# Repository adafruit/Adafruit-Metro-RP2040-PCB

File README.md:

## Adafruit Metro RP2040 PCB

<a href="http://www.adafruit.com/products/5786"><br/>
Click here to purchase one from the Adafruit shop</a>

PCB files for the Adafruit Metro RP2040. 

Format is EagleCAD schematic and board layout
* https://www.adafruit.com/product/5786

### Description

Choo! Choo! This is the RP2040 Metro Line, making all station stops at "Dual Cortex M0+ mountain", "264K RAM round-about" and "16 Megabytes of Flash town". This train is pile high with hardware that complements the Raspberry Pi RP2040 chip to make it an excellent development board for projects that want Arduino-shape-compatibility or just need the extra space and debugging ports.

* RP2040 main chip, 133MHz clock, 3.3V logic
* 16 MB of QSPI flash for program storage
* 24 GPIO, 4 of which are also analog inputs
* Micro SD card wired up for SPI interfacing, also has extra pins connected for advanced-user SDIO interfacing (note that there's no released usage code for SDIO in Arduino/Python, so this is a super-cutting-edge setup)
* Onboard RGB NeoPixel
* Onboard #13 LED
* Stemma QT port for I2C peripherals and sensors
* Reset and Boot buttons on PCB edge
* Pico Probe debug port - 3 pin JST SH compatible
* SWD debug port - 2x5 0.05" standard connector
* USB Type C power and data
* 5.5mm / 2.1mm DC jack for 6-12VDC power
* On/off switch for DC jack
* GPIO pin numbers match classic Arduino pins, other than A4/A5 which are D24 and D25 (there's only 4 ADC pins on the RP2040)
* RX / TX switch for swapping D0 and D1 locations

You may be wondering about the RX-TX switch: we added this because traditional Arduino board start counting the GPIO for the digital pins with 0-7 and then 8-13. However, the D0/D1 pins are also traditionally the hardware UART Serial1, where D0 is Rx and D1 is Tx. On the RP2040, however, the UART pins are the other around: D0 is Tx and D1 is Rx. Thus a DPDT switch: flip one way to have the GPIO go in order of 0-7, flip the other way to have the logical locations of the hardware UART correct but now the pin order is 1, 0, 2, 3..7. Of course, it's also handy if, like us, you often swap the pins - now you don't need to require or cut/solder traces!
About the RP2040

The RP2040 is a powerful chip, which has the clock speed of our M4 (SAMD51), and two cores that are equivalent to our M0 (SAMD21). Since it is an M0 chip, it does not have a floating point unit or DSP hardware support - so if you're doing something with heavy floating-point math, it will be done in software and thus not as fast as an M4. For many other computational tasks, you'll get close-to-M4 speeds!

For peripherals, there are two I2C controllers, two SPI controllers, and two UARTs that are multiplexed across the GPIO - check the pinout for what pins can be set to which. There are 16 PWM channels, each pin has a channel it can be set to (ditto on the pinout).

You'll note there's no I2S peripheral, or SDIO, or camera, what's up with that? Well, instead of having specific hardware support for serial-data-like peripherals like these, the RP2040 comes with the PIO state machine system, which is a unique and powerful way to create custom hardware logic and data processing blocks that run on their own without taking up a CPU. For example, NeoPixels - often we bitbang the timing-specific protocol for these LEDs. For the RP2040, we instead use PIO object that reads in the data buffer and clocks out the right bitstream with perfect accuracy. Same with I2S audio in or out, LED matrix displays, 8-bit or SPI based TFTs, even VGA! In MicroPython and CircuitPython, you can create PIO control commands to script the peripheral and load it in at runtime. There are 2 PIO peripherals with 4 state machines each.

There is great C/C++ support, unofficial (but really good) Arduino support, an official MicroPython port, and a CircuitPython port! We, of course, recommend CircuitPython because we think it's the easiest way to get started, and it has support with most of our drivers, displays, sensors, and more, supported out of the box so you can follow along with our CircuitPython projects and tutorials.

While the RP2040 has lots of onboard RAM (264KB), it does not have built-in FLASH memory. Instead, that is provided by the external QSPI flash chip. On this board, there is 16 MB, which is shared between the program it's running and any file storage used by MicroPython or CircuitPython. When using C/C++, you get the whole flash memory, if using Python, you will have about 7 MB remaining for code, files, images, fonts, etc.
RP2040 Chip features:

* Dual ARM Cortex-M0+ @ 133MHz
* 264kB on-chip SRAM in six independent banks
* Support for up to 16MB of off-chip Flash memory via dedicated QSPI bus
* DMA controller
* Fully-connected AHB crossbar
* Interpolator and integer divider peripherals
* On-chip programmable LDO to generate core voltage
* 2 on-chip PLLs to generate USB and core clocks
* 30 GPIO pins, 4 of which can be used as analog inputs
* Peripherals
  * 2 UARTs
  * 2 SPI controllers
  * 2 I2C controllers
  * 16 PWM channels
  * USB 1.1 controller and PHY, with host and device support
  * 8 PIO state machines

### License

Adafruit invests time and resources providing this open source design, please support Adafruit and open-source hardware by purchasing products from [Adafruit](https://www.adafruit.com)!

Designed by Limor Fried/Ladyada for Adafruit Industries.

Creative Commons Attribution/Share-Alike, all text above must be included in any redistribution. 
See license.txt for additional details.

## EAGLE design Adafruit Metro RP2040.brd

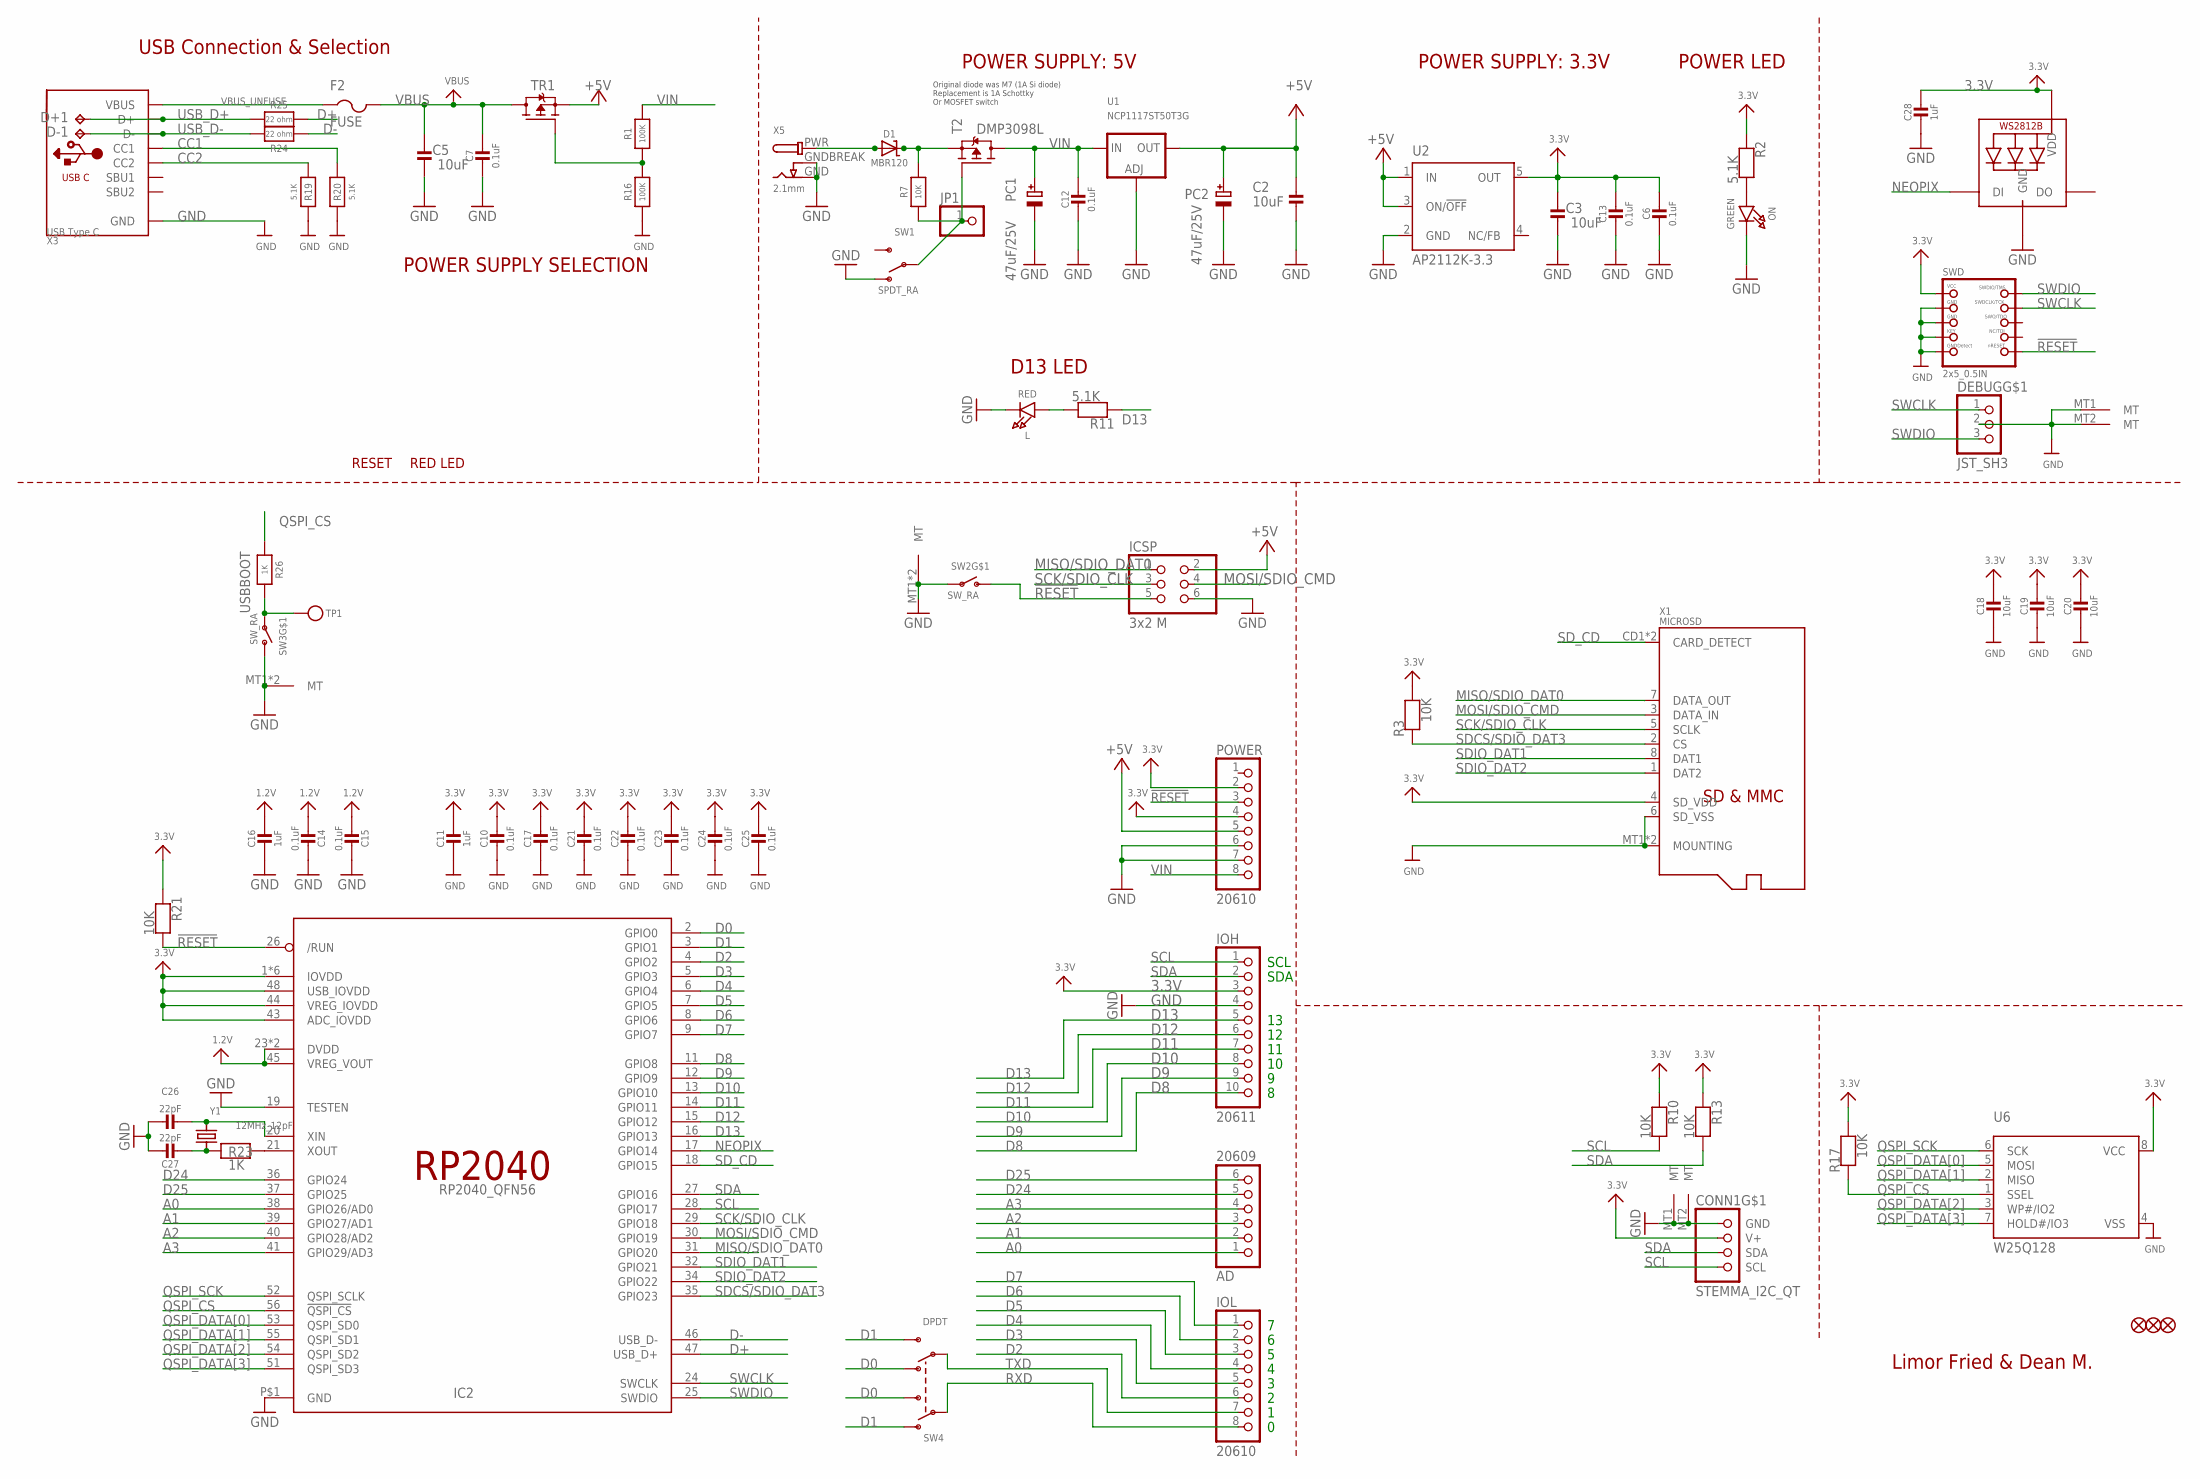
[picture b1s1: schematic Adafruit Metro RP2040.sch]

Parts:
AD: 20609; 1X06_OVALWAVE
C2, C3, C5, C18, C19, C20: 10uF; 0805-NO
C6, C7, C10, C12, C13, C14, C15, C17, C21, C22, C23, C24, C25: 0.1uF; 0603-NO
C11, C16, C28: 1uF; 0603-NO
C26, C27: 22pF; 0603-NO
CONN1: STEMMA_I2C_QT; JST_SH4
D1: MBR120; SOD-123
D+1: TPB1,27; B1,27
D-1: TPB1,27; B1,27
DEBUG: JST_SH3
F2: FUSE; R1206
FD1, FD2, FD3: FIDUCIAL_1MM
IC2: RP2040_QFN56; QFN56_7MM_REDUCEDEPAD
ICSP: 3x2 M; 2X03_ROUND_70MIL
IOH: 20611; 1X10_OVALWAVE
IOL: 20610; 1X08_OVALWAVE
JP1: HEADER-1X1ROUND; 1X01_ROUND
L: RED; CHIPLED_0603_NOOUTLINE
LED2: WS2812B_3535FULL; LED3535_FULLPADS
ON: GREEN; CHIPLED_0603_NOOUTLINE
PC1, PC2: 47uF/25V; PANASONIC_D
POWER: 20610; 1X08_OVALWAVE
R1, R16: 100K; 0603-NO
R2, R11, R19, R20: 5.1K; 0603-NO
R3, R7, R10, R13, R17, R21: 10K; 0603-NO
R23, R26: 1K; 0603-NO
R24, R25: 22 ohm; 0603-NO
SW1: SPDT_RA; SPDT_SMT_SSSS811101
SW2, SW3: SW_RA; SPST_TACTILE_RA
SW4: DPDT; EG1390
SWD: 2x5_0.5IN; 2X05_1.27MM_BOX_POSTS
T2: DMP3098L; SOT23-WIDE
TP1: TESTPOINTROUND1.5MMNO; TESTPOINT_ROUND_1.5MM_NO
TR1: DMP3098L; SOT23-WIDE
U1: NCP1117ST50T3G; SOT223-R
U2: AP2112K-3.3; SOT23-DBV
U6: W25Q128; SOIC8_208MIL
X1: MICROSD
X3: USB Type C; USB_C_CUSB31-CFM2AX-01-X
X5: 2.1mm; DCJACK_2MM_PTH
Y1: 12MHz_12pF; CRYSTAL_2.5X2

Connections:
1.2V: C14.2, C15.2, C16.1, IC2.23 (DVDD), IC2.45 (VREG_VOUT), IC2.50 (DVDD)
3.3V: C3.2, C6.2, C10.1, C11.1, C13.1, C17.1, C18.1, C19.1, C20.1, C21.1, C22.1, C23.1, C24.1, C25.1, C28.1, CONN1.2 (V+), IC2.1 (IOVDD), IC2.10 (IOVDD), IC2.22 (IOVDD), IC2.33 (IOVDD), IC2.42 (IOVDD), IC2.43 (ADC_IOVDD), IC2.44 (VREG_IOVDD), IC2.48 (USB_IOVDD), IC2.49 (IOVDD), IOH.3, LED2.2 (VDD), POWER.2, POWER.4, R2.1, R3.2, R10.1, R13.1, R17.2, R21.1, SWD.1 (VCC), U2.5 (OUT), U6.8 (VCC), X1.4 (SD_VDD)
!RESET: IC2.26 (/RUN), ICSP.5, POWER.3, R21.2, SW2.2 (S), SWD.10 (NRESET)
+5V: C2.2, ICSP.2, PC2.+, POWER.5, TR1.2 (S), U1.2 (OUT), U1.4 (OUT), U2.1 (IN), U2.3 (ON/!OFF)
A0: AD.1, IC2.38 (GPIO26/AD0)
A1: AD.2, IC2.39 (GPIO27/AD1)
A2: AD.3, IC2.40 (GPIO28/AD2)
A3: AD.4, IC2.41 (GPIO29/AD3)
CC1: R20.2, X3.A5 (CC1)
CC2: R19.2, X3.B5 (CC2)
D0: IC2.2 (GPIO0), SW4.O2, SW4.S1
D1: IC2.3 (GPIO1), SW4.O1, SW4.S2
D2: IC2.4 (GPIO2), IOL.6
D3: IC2.5 (GPIO3), IOL.5
D4: IC2.6 (GPIO4), IOL.4
D5: IC2.7 (GPIO5), IOL.3
D6: IC2.8 (GPIO6), IOL.2
D7: IC2.9 (GPIO7), IOL.1
D8: IC2.11 (GPIO8), IOH.10
D9: IC2.12 (GPIO9), IOH.9
D10: IC2.13 (GPIO10), IOH.8
D11: IC2.14 (GPIO11), IOH.7
D12: IC2.15 (GPIO12), IOH.6
D13: IC2.16 (GPIO13), IOH.5, R11.1
D24: AD.5, IC2.36 (GPIO24)
D25: AD.6, IC2.37 (GPIO25)
D+: IC2.47 (USB_D+), R25.2
D-: IC2.46 (USB_D-), R24.2
GND: C2.1, C3.1, C5.1, C6.1, C7.2, C10.2, C11.2, C12.2, C13.2, C14.1, C15.1, C16.2, C17.2, C18.2, C19.2, C20.2, C21.2, C22.2, C23.2, C24.2, C25.2, C26.1, C27.1, C28.2, CONN1.1 (GND), CONN1.MT1 (MT), CONN1.MT2 (MT), DEBUG.2, DEBUG.MT1 (MT), DEBUG.MT2 (MT), IC2.19 (TESTEN), IC2.P$1 (GND), ICSP.6, IOH.4, L.C, LED2.4 (GND), ON.C, PC1.-, PC2.-, POWER.6, POWER.7, R16.1, R19.1, R20.1, SW1.A (O), SW2.1, SW2.MT1 (MT), SW2.MT2 (MT), SW3.2 (S), SW3.MT1 (MT), SW3.MT2 (MT), SWD.3 (GND), SWD.5 (GND), SWD.7 (KEY), SWD.9 (GNDDETECT), U1.1 (ADJ), U2.2 (GND), U6.4 (VSS), X1.6 (SD_VSS), X1.MT1 (MOUNTING), X1.MT2 (MOUNTING), X3.A1B12 (GND), X3.B1A12 (GND), X5.GND, X5.GNDBREAK
MISO/SDIO_DAT0: IC2.31 (GPIO20), ICSP.1, X1.7 (DATA_OUT)
MOSI/SDIO_CMD: IC2.30 (GPIO19), ICSP.4, X1.3 (DATA_IN)
unnamed: L.A, R11.2
unnamed: ON.A, R2.2
unnamed: C26.2, IC2.20 (XIN), Y1.3 (2)
unnamed: C27.2, R23.1, Y1.1
unnamed: R1.1, R16.2, TR1.1 (G)
unnamed: IC2.21 (XOUT), R23.2
unnamed: D1.C, R7.2, T2.2 (S)
NEOPIX: IC2.17 (GPIO14), LED2.1 (DI)
PWRIN: D1.A, X5.PWR
PWR_SWITCH: JP1.1, R7.1, SW1.B, T2.1 (G)
QSPI_CS: IC2.56 (!QSPI_CS), R17.1, R26.1, U6.1 (SSEL)
QSPI_DATA[0]: IC2.53 (QSPI_SD0), U6.5 (MOSI)
QSPI_DATA[1]: IC2.55 (QSPI_SD1), U6.2 (MISO)
QSPI_DATA[2]: IC2.54 (QSPI_SD2), U6.3 (WP#/IO2)
QSPI_DATA[3]: IC2.51 (QSPI_SD3), U6.7 (HOLD#/IO3)
QSPI_SCK: IC2.52 (QSPI_SCLK), U6.6 (SCK)
RXD: IOL.8, SW4.P1
SCK/SDIO_CLK: IC2.29 (GPIO18), ICSP.3, X1.5 (SCLK)
SCL: CONN1.4 (SCL), IC2.28 (GPIO17), IOH.1, R10.2
SDA: CONN1.3 (SDA), IC2.27 (GPIO16), IOH.2, R13.2
SDCS/SDIO_DAT3: IC2.35 (GPIO23), R3.1, X1.2 (CS)
SDIO_DAT1: IC2.32 (GPIO21), X1.8 (DAT1)
SDIO_DAT2: IC2.34 (GPIO22), X1.1 (DAT2)
SD_CD: IC2.18 (GPIO15), X1.CD1 (CARD_DETECT), X1.CD2 (CARD_DETECT)
SWCLK: DEBUG.1, IC2.24 (SWCLK), SWD.4 (SWDCLK)
SWDIO: DEBUG.3, IC2.25 (SWDIO), SWD.2 (SWDIO)
TXD: IOL.7, SW4.P2
USBBOOT: R26.2, SW3.1, TP1.P$1
USB_D+: D+1.TP, R25.1, X3.A6 (D+), X3.B6 (D+)
USB_D-: D-1.TP, R24.1, X3.A7 (D-), X3.B7 (D-)
VBUS: C5.2, C7.1, F2.2, TR1.3 (D)
VBUS_UNFUSE: F2.1, X3.A4B9 (VBUS), X3.B4A9 (VBUS)
VIN: C12.1, PC1.+, POWER.8, R1.2, T2.3 (D), U1.3 (IN)

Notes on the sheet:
SDA
SCL
Limor Fried & Dean M.
Original diode was M7 (1A Si diode) Replacement is 1A Schottky Or MOSFET switch
POWER SUPPLY: 5V
USB Connection & Selection
POWER SUPPLY: 3.3V
POWER LED
POWER SUPPLY SELECTION
D13 LED
RESET
RED LED

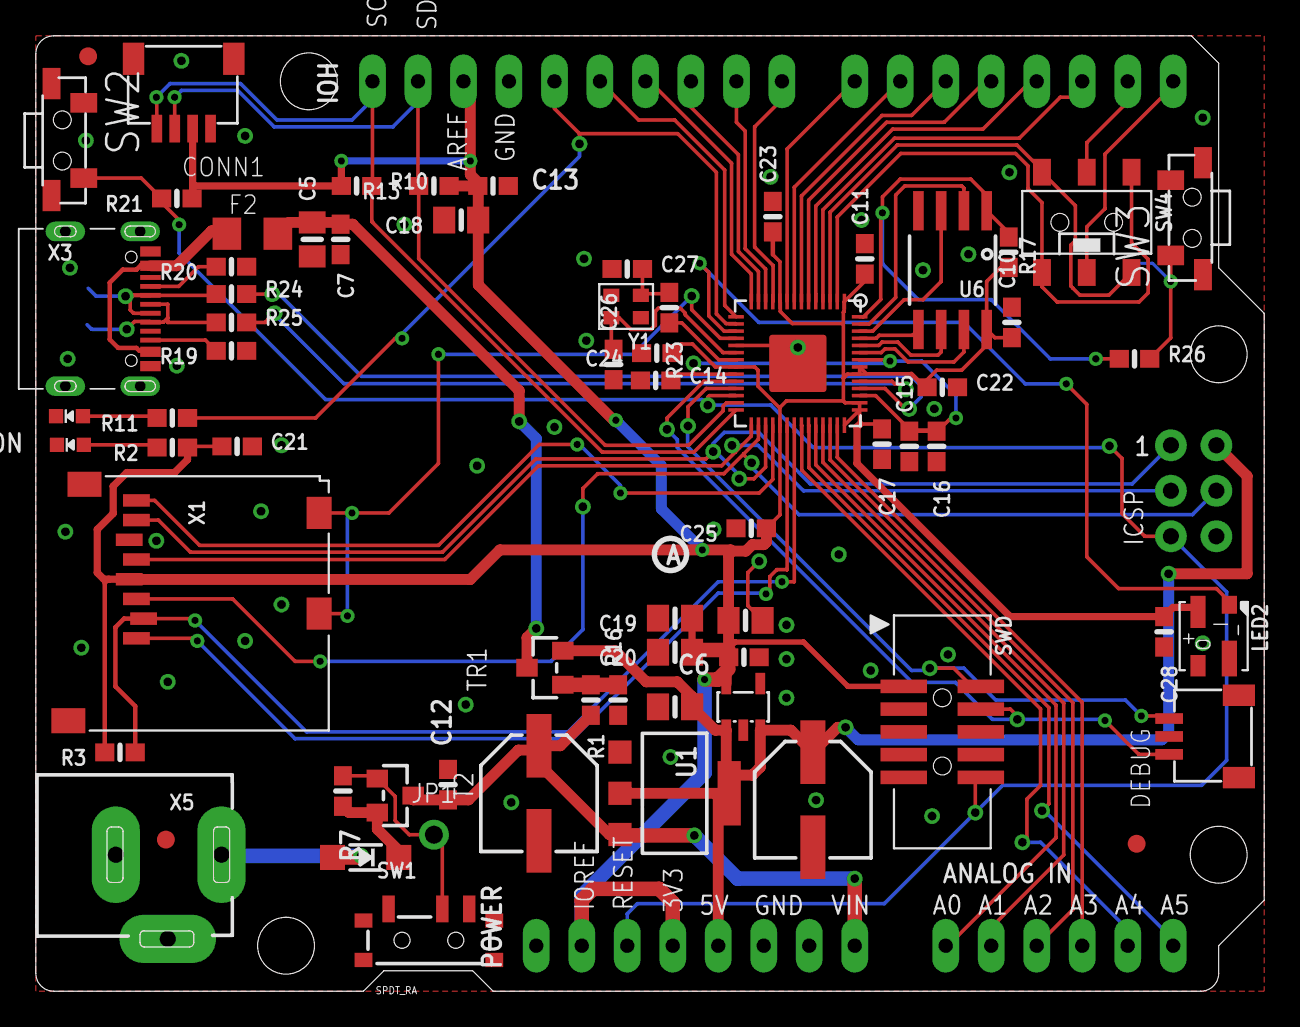
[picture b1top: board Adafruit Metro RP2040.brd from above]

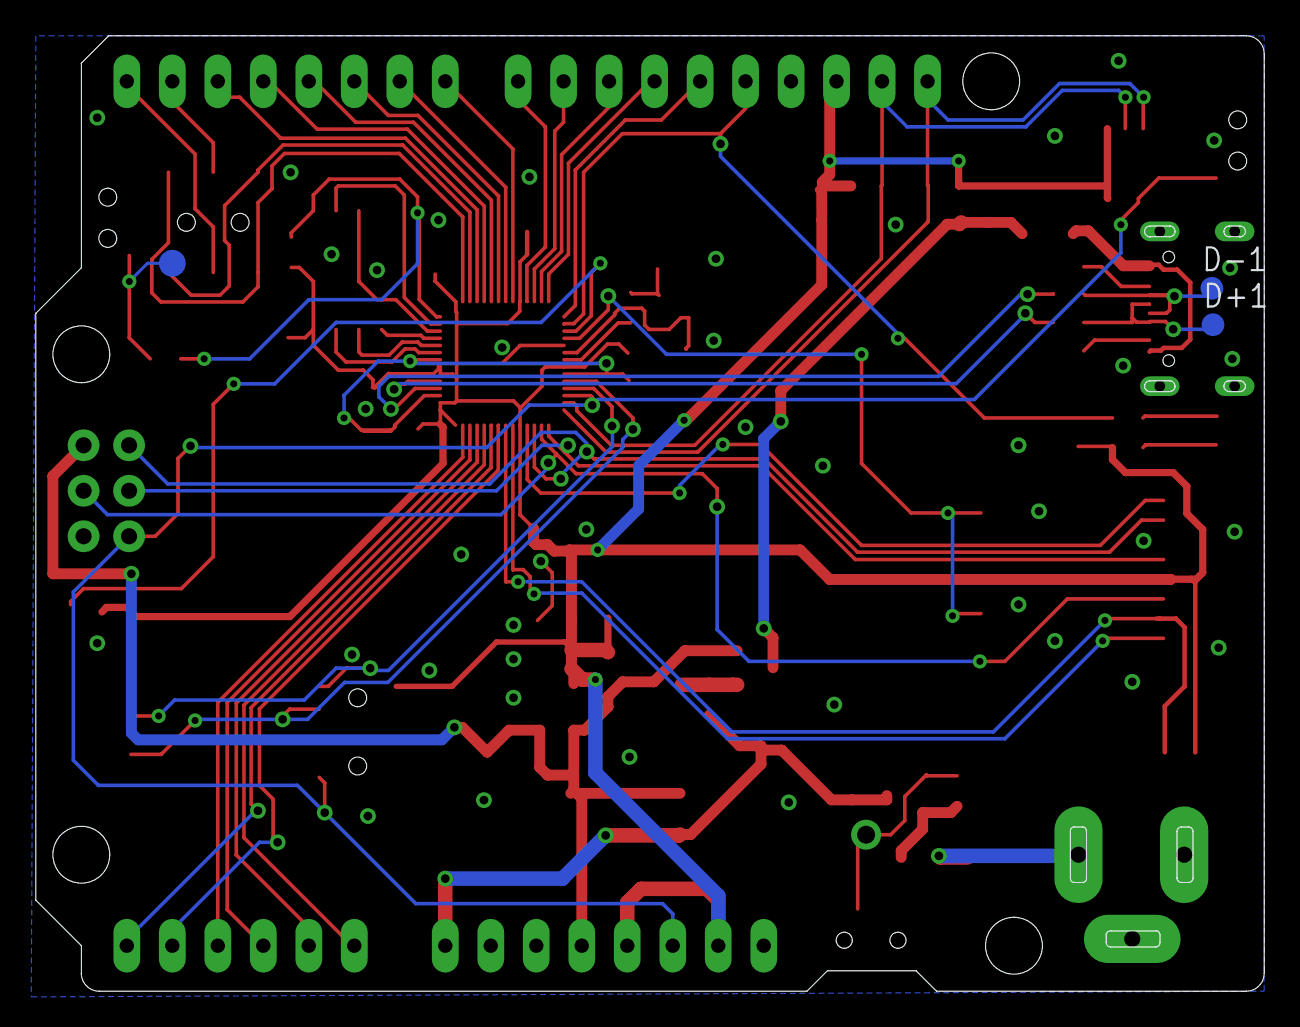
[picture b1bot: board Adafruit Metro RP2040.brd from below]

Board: 2 copper layers, 68.6 x 53.3 mm, 79 parts (4 on the bottom side), 64 nets.

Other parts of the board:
U$11: PCBFEAT-REV-040
U$15: METRO_RP2040_BOT
U$29: METRO_RP2040_TOP

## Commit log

2023-08-02 Add board files.
2023-08-04 Add PrettyPins.
2023-08-11 Add factory reset UF2.
2023-08-11 Rename.

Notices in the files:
parts and their libraries:
microbuilder: This work is placed in the public domain, and may be freely used for commercial and non-commercial work with the following conditions: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
SparkFun-Aesthetics: Licensing: CC v3.0 Share-Alike You are welcome to use this library for commercial purposes.
